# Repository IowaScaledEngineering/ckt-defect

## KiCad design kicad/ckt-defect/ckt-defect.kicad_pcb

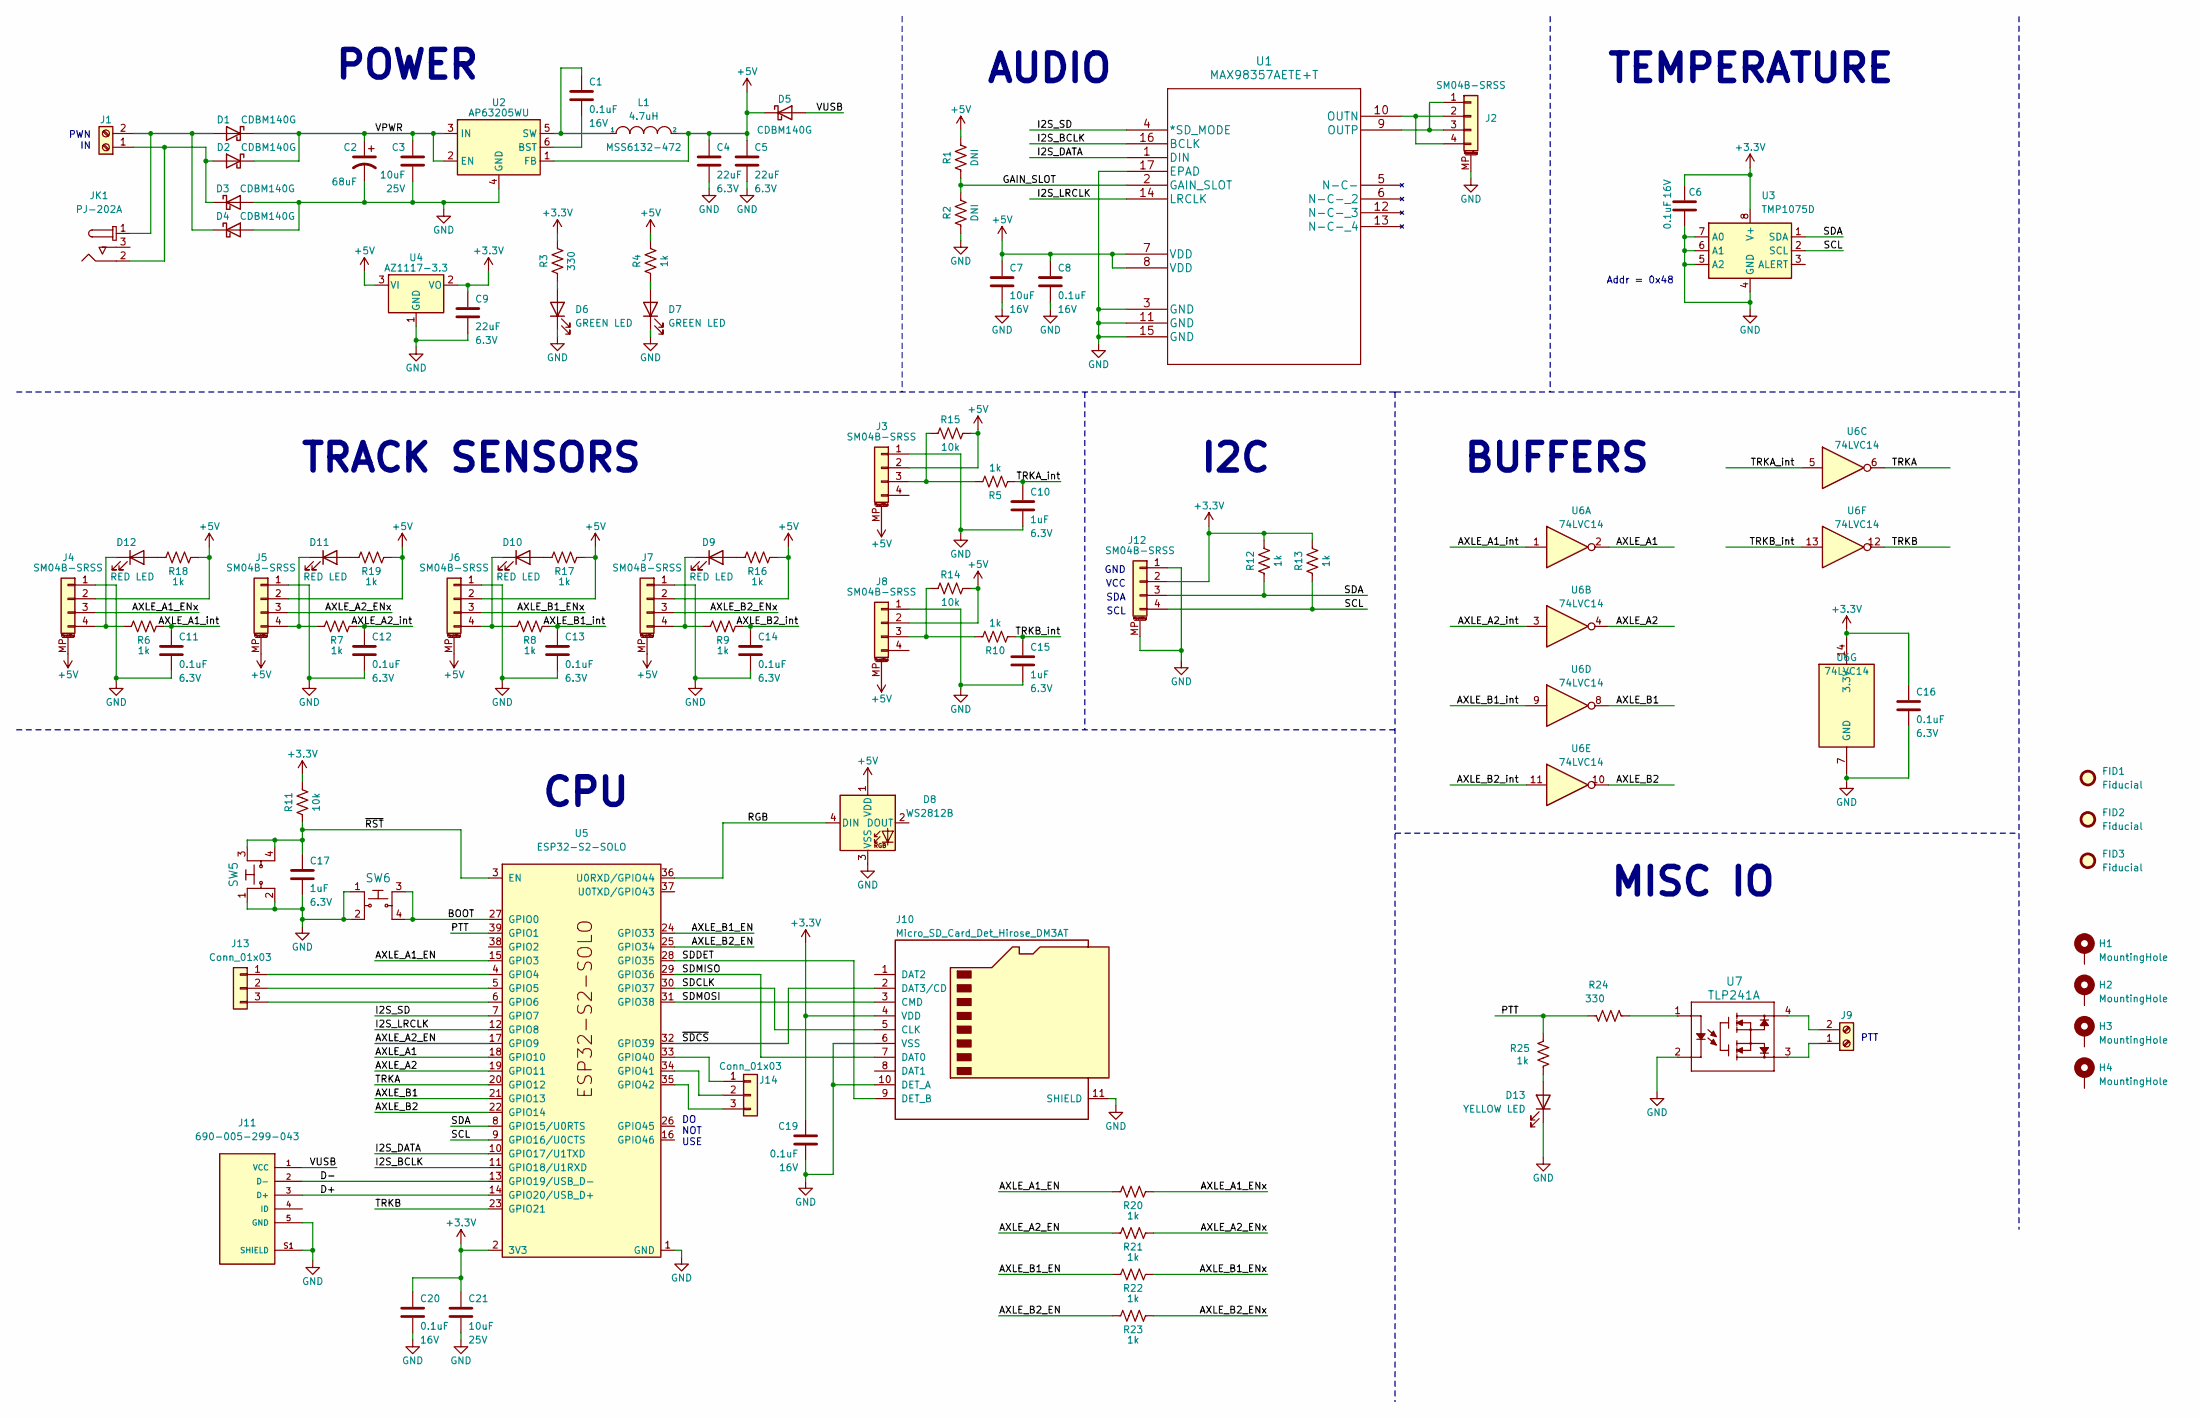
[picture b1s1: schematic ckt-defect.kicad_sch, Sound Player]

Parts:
C1, C6, C8, C19, C20: 0.1uF; C_0805_2012Metric; Voltage 16V
C2: 68uF; CP_Elec_6.3x5.8
C3, C21: 10uF; C_0805_2012Metric; Voltage 25V
C4, C5, C9: 22uF; C_0805_2012Metric; Voltage 6.3V
C7: 10uF; C_0805_2012Metric; Voltage 16V
C10, C15, C17: 1uF; C_0805_2012Metric; Voltage 6.3V
C11, C12, C13, C14, C16: 0.1uF; C_0805_2012Metric; Voltage 6.3V
D1, D2, D3, D4, D5: CDBM140G; SOD-123T
D6, D7: GREEN LED; LED_0805_2012Metric
D8: WS2812B; LED_WS2812B_PLCC4_5.0x5.0mm_P3.2mm
D9, D10, D11, D12: RED LED; LED_0805_2012Metric
D13: YELLOW LED; LED_0805_2012Metric
FID1, FID2, FID3: Fiducial; Fiducial_1mm_Mask2mm
H1, H2, H3, H4: MountingHole; MountingHole_3.2mm_M3_Pad
J1, J9: Screw_Terminal_01x02; TerminalBlock_RND_205-00012_1x02_P5.00mm_Horizontal
J2, J3, J4, J5, J6, J7, J8, J12: SM04B-SRSS; JST_SH_SM04B-SRSS-TB_1x04-1MP_P1.00mm_Horizontal
J10: Micro_SD_Card_Det_Hirose_DM3AT; microSD_HC_Hirose_DM3AT-SF-PEJM5
J11: 690-005-299-043; EDAC_690-005-299-043; PARTREV 11
J13, J14: Conn_01x03; PinHeader_1x03_P1.27mm_Vertical
JK1: PJ-202A; CUI_PJ-202A; MPN PJ-202A; Digi-Key_PN CP-202A-ND
L1: 4.7uH; MSS6132-xxxMLC
R1, R2: DNI; R_0805_2012Metric
R3, R24: 330; R_0805_2012Metric
R4, R5, R6, R7, R8, R9, R10, R12, R13, R16, R17, R18, R19, R20, R21, R22, R23, R25: 1k; R_0805_2012Metric
R11, R14, R15: 10k; R_0805_2012Metric
SW5, SW6: FSM4JSMA; TE_FSM4JSMA; MPN FSM4JSMATR; Digi-Key_PN 450-1759-1-ND
U1: MAX98357AETE+T; TQFN-16-1EP_3x3mm_P0.5mm_EP1.23x1.23mm
U2: AP63205WU; TSOT-23-6
U3: TMP1075D; SO-8_3.9x4.9mm_P1.27mm
U4: AZ1117-3.3; SOT-223-3_TabPin2
U5: ESP32-S2-SOLO
U6: 74LVC14; SOIC-14_3.9x8.7mm_P1.27mm
U7: TLP241A; 11-5B201S_TOS

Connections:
+3.3V: C6.1, C9.1, C16.1, C19.1, C20.1, C21.1, J10.4 (VDD), J12.2, R3.2, R11.2, R12.2, R13.2, U3.8 (V+), U4.2 (VO), U5.2 (3V3), U6.14 (3.3V)
+5V: C4.1, C5.1, C7.1, C8.1, D5.1 (K), D8.1 (VDD), J3.2, J3.MP (MountPin), J4.2, J4.MP (MountPin), J5.2, J5.MP (MountPin), J6.2, J6.MP (MountPin), J7.2, J7.MP (MountPin), J8.2, J8.MP (MountPin), L1.2, R1.2, R4.2, R14.2, R15.2, R16.1, R17.1, R18.1, R19.1, U1.7 (VDD), U1.8 (VDD), U2.1 (FB), U4.3 (VI)
/AXLE_A1: U5.18 (GPIO10), U6.2
/AXLE_A1_EN: R20.2, U5.15 (GPIO3)
/AXLE_A1_ENx: J4.3, R20.1
/AXLE_A1_int: C11.1, R6.1, U6.1
/AXLE_A2: U5.19 (GPIO11), U6.4
/AXLE_A2_EN: R21.2, U5.17 (GPIO9)
/AXLE_A2_ENx: J5.3, R21.1
/AXLE_A2_int: C12.1, R7.1, U6.3
/AXLE_B1: U5.21 (GPIO13), U6.8
/AXLE_B1_EN: R22.2, U5.24 (GPIO33)
/AXLE_B1_ENx: J6.3, R22.1
/AXLE_B1_int: C13.1, R8.1, U6.9
/AXLE_B2: U5.22 (GPIO14), U6.10
/AXLE_B2_EN: R23.2, U5.25 (GPIO34)
/AXLE_B2_ENx: J7.3, R23.1
/AXLE_B2_int: C14.1, R9.1, U6.11
/BOOT: SW6.3, SW6.4, U5.27 (GPIO0)
/D+: J11.3 (D+), U5.14 (GPIO20/USB_D+)
/D-: J11.2 (D-), U5.13 (GPIO19/USB_D-)
/GAIN_SLOT: R1.1, R2.2, U1.2 (GAIN_SLOT)
/I2S_BCLK: U1.16 (BCLK), U5.11 (GPIO18/U1RXD)
/I2S_DATA: U1.1 (DIN), U5.10 (GPIO17/U1TXD)
/I2S_LRCLK: U1.14 (LRCLK), U5.12 (GPIO8)
/I2S_SD: U1.4 (*SD_MODE), U5.7 (GPIO7)
/PTT: R24.2, R25.1, U5.39 (GPIO1)
/RGB: D8.4 (DIN), U5.36 (U0RXD/GPIO44)
/SCL: J12.4, R13.1, U3.2 (SCL), U5.9 (GPIO16/U0CTS)
/SDA: J12.3, R12.1, U3.1 (SDA), U5.8 (GPIO15/U0RTS)
/SDCLK: J10.5 (CLK), U5.30 (GPIO37)
/SDDET: J10.9 (DET_B), U5.28 (GPIO35)
/SDMISO: J10.7 (DAT0), U5.29 (GPIO36)
/SDMOSI: J10.3 (CMD), U5.31 (GPIO38)
/TRKA: U5.20 (GPIO12), U6.6
/TRKA_int: C10.1, R5.1, U6.5
/TRKB: U5.23 (GPIO21), U6.12
/TRKB_int: C15.1, R10.1, U6.13
/VPWR: C2.1, C3.1, D1.1 (K), D2.1 (K), U2.2 (EN), U2.3 (IN)
/VUSB: D5.2 (A), J11.1 (VCC)
/~RST: C17.1, R11.1, SW5.3, SW5.4, U5.3 (EN)
/~SDCS: J10.2 (DAT3/CD), U5.32 (GPIO39)
GND: C2.2, C3.2, C4.2, C5.2, C6.2, C7.2, C8.2, C9.2, C10.2, C11.2, C12.2, C13.2, C14.2, C15.2, C16.2, C17.2, C19.2, C20.2, C21.2, D3.2 (A), D4.2 (A), D6.1 (K), D7.1 (K), D8.3 (VSS), D13.1 (K), J2.MP (MountPin), J3.1, J4.1, J5.1, J6.1, J7.1, J8.1, J10.6 (VSS), J10.10 (DET_A), J10.11 (SHIELD), J11.5 (GND), J11.S1 (SHIELD), J12.1, J12.MP (MountPin), R2.1, SW5.1, SW5.2, SW6.1, SW6.2, U1.3 (GND), U1.11 (GND), U1.15 (GND), U1.17 (EPAD), U2.4 (GND), U3.4 (GND), U3.5 (A2), U3.6 (A1), U3.7 (A0), U4.1 (GND), U5.1 (GND), U5.40 (GND), U5.41 (GND), U6.7 (GND), U7.2
unnamed: D1.2 (A), D4.1 (K), J1.2, JK1.1
unnamed: D2.2 (A), D3.1 (K), J1.1, JK1.2
unnamed: D6.2 (A), R3.1
unnamed: D7.2 (A), R4.1
unnamed: D9.2 (A), R16.2
unnamed: D9.1 (K), J7.4, R9.2
unnamed: D10.2 (A), R17.2
unnamed: D10.1 (K), J6.4, R8.2
unnamed: D11.2 (A), R19.2
unnamed: D11.1 (K), J5.4, R7.2
unnamed: D12.2 (A), R18.2
unnamed: D12.1 (K), J4.4, R6.2
unnamed: D13.2 (A), R25.2
unnamed: J2.1, J2.3, U1.9 (OUTP)
unnamed: J2.2, J2.4, U1.10 (OUTN)
unnamed: J3.3, R5.2, R15.1
unnamed: J8.3, R10.2, R14.1
unnamed: J9.1, U7.3
unnamed: J9.2, U7.4
unnamed: J13.1, U5.4 (GPIO4)
unnamed: J13.2, U5.5 (GPIO5)
unnamed: J13.3, U5.6 (GPIO6)
unnamed: J14.1, U5.33 (GPIO40)
unnamed: J14.2, U5.34 (GPIO41)
unnamed: J14.3, U5.35 (GPIO42)
unnamed: R24.1, U7.1
unnamed: C1.2, U2.6 (BST)
unnamed: C1.1, L1.1, U2.5 (SW)

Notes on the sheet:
BUFFERS
DO NOT USE
GND
PTT
I2C
TEMPERATURE
PWN IN
POWER
TRACK SENSORS
Addr = 0x48
CPU
SDA
MISC IO
AUDIO
VCC
SCL

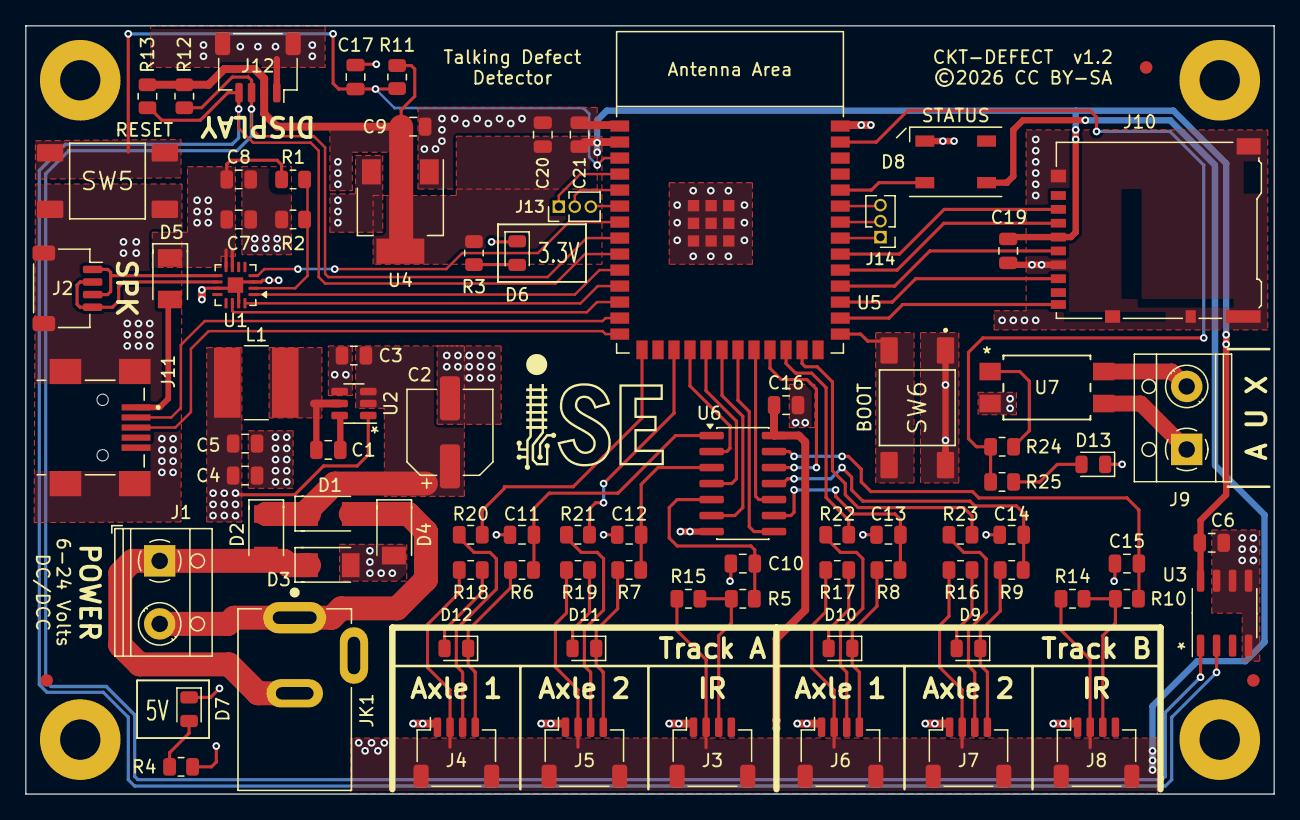
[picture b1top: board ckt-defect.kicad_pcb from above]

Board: 2 copper layers, 99.1 x 61.0 mm, 90 parts (0 on the bottom side), 71 nets.

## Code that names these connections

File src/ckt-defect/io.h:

/*************************************************************************
Title:    Input/Output Functions
Authors:  Michael Petersen <railfan@drgw.net>
File:     io.h
License:  GNU General Public License v3

LICENSE:
    Copyright (C) 2026 Michael Petersen & Nathan Holmes

    This program is free software; you can redistribute it and/or modify
    it under the terms of the GNU General Public License as published by
    the Free Software Foundation; either version 2 of the License, or
    any later version.

    This program is distributed in the hope that it will be useful,
    but WITHOUT ANY WARRANTY; without even the implied warranty of
    MERCHANTABILITY or FITNESS FOR A PARTICULAR PURPOSE.  See the
    GNU General Public License for more details.

*************************************************************************/

#pragma once

// Pins
#define SDA          GPIO_NUM_15
#define SCL          GPIO_NUM_16
#define I2S_SD       GPIO_NUM_7
#define I2S_DOUT     GPIO_NUM_17
#define I2S_BCLK     GPIO_NUM_18
#define I2S_LRCLK    GPIO_NUM_8
#define SDCLK        37
#define SDMOSI       38
#define SDMISO       36
#define SDCS         39
#define SDDET        GPIO_NUM_35

#define AXLE_A1      GPIO_NUM_10
#define AXLE_A1_EN   GPIO_NUM_3
#define AXLE_A2      GPIO_NUM_11
#define AXLE_A2_EN   GPIO_NUM_9
#define AXLE_B1      GPIO_NUM_13
#define AXLE_B1_EN   GPIO_NUM_33
#define AXLE_B2      GPIO_NUM_14
#define AXLE_B2_EN   GPIO_NUM_34
#define TRKA         GPIO_NUM_12
#define TRKB         GPIO_NUM_21

#define AUX          GPIO_NUM_1

#define TP0          GPIO_NUM_4
#define TP1          GPIO_NUM_5
#define TP2          GPIO_NUM_6
#define TP3          GPIO_NUM_40
#define TP4          GPIO_NUM_41
#define TP5          GPIO_NUM_42

void ioInit(void);

void enableAuxRelay(void);
void disableAuxRelay(void);

void ioProcessInputs(void);
bool getIrA(void);
bool getAxleA1(void);
bool getAxleA2(void);
bool getIrB(void);
bool getAxleB1(void);
bool getAxleB2(void);

void setTestPoint(gpio_num_t tp);
void clrTestPoint(gpio_num_t tp);

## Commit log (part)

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2025-06-30 Sent to fab
2025-12-28 Renamed to ckt-defect
2025-12-28 Copied latest code from snd-player
2025-12-28 Updated makefile
2025-12-29 Task based audio feeder
2025-12-29 Removed PLAYER_RETRY state and used blocking feature of i2s_channel_write
2025-12-29 Cleaned up task delay when in idle state
2025-12-29 Split out I2S code into its own file
2025-12-29 Moved volume handling to audio files. Cleaned up restart code.
2025-12-29 Cleanup
2025-12-30 Some cleanup in the silence generation
2026-02-12 Copy from snd-player and modified
2026-02-12 Kicad 9 conversion; added test points
2026-03-07 Some rip-up and refactoring, with a dash of architecture
2026-03-08 More progress
2026-03-08 Minor updates
2026-03-08 vocab support files
2026-03-08 Refactored audio code to wrap queue handling in functions
2026-03-08 Some changes
2026-03-08 Moved sound functions into cpp
2026-03-08 More improvements
2026-03-08 sound function refactoring to use std::string
2026-03-08 First cut at internal vocab
2026-03-08 vocab cleanup
2026-03-09 Initial parser code
2026-03-09 Some updates
2026-03-09 Searchable vocab
2026-03-09 Parsing and reading messages
2026-03-12 Updated parser to accept a ParserObject and optionally delete the message when done.
2026-03-13 Some documents
2026-03-14 Added message transformation
2026-03-14 More parsing and a better test state machine
2026-03-14 Removed debug message
2026-03-14 Added tone support
2026-03-14 Added "detector out" to exit message
2026-03-15 Initial axle simulator
2026-03-15 Working axle simulator
2026-03-15 Axle calculator
2026-03-15 Changed axle counters to use 3.3V supply
2026-03-15 Updated date
2026-03-15 Moved axles simulator over to ckt-axle project
2026-03-15 IO functions and LCD test code
2026-03-15 Aux relay support
2026-03-16 Added test points for profiling
2026-03-16 Changed edge cleanance
2026-03-16 Adjusted the 5V bus at the bottom
2026-03-16 Initial axle counter interrupts
2026-03-18 Added input schmitt inverters
2026-03-18 Moved logo
2026-03-18 Changed to micros()
2026-03-19 Improved buffering
2026-03-19 PG 1.1
2026-03-21 Added PTT support to the audio driver
2026-03-21 Refactored axle counter code
2026-03-22 Changed to Kicad footprint for QFN
2026-04-05 Added sound effects
2026-04-06 Added programmability to tone generation
2026-04-06 Added programmable silence
2026-04-14 Refactoring for SD card
2026-04-14 Axle counter code fixed
2026-05-17 Added menu code - untested
2026-05-18 Updated menu code
2026-05-18 Remove executable
2026-05-18 Initial cache LCD implementation
2026-05-18 gotoxy fixes
2026-05-18 Improved string writes
2026-05-18 Fixed excess overwrites
2026-05-23 Removed brackets from MenuNumberDial
2026-05-23 Added leading zero suppression option in MenuDigitThumbwheel
2026-05-23 Added backlight code
2026-05-23 Fixed brightness value when writing I2C
2026-05-23 Added NACK detection and refreshing
2026-05-23 Added custom character support
2026-05-23 Fixed hardware vs software brightness levels
2026-05-23 Initial brightness menu
2026-05-23 Updated brightness menu with 16 levels
2026-05-23 Swapped +/- button on NumberDial
2026-05-23 Removed debug code
2026-05-23 Default backlight off
2026-05-23 Added MenuPercentageBar
2026-05-23 Removed MenuBacklight and updated MenuPercentageBar to accept getter/setter functions
2026-05-24 Added getter/setter support to all menus
2026-05-24 Moved realTime argument
2026-05-24 Formatting cleanup
2026-05-24 Changed display connect wait to 100ms
2026-05-24 Added realTimeUpdate to all versions of constructors
2026-05-24 Added save callback
2026-05-24 Added LCD brightness handling
2026-05-24 Added continuous increment/decrement
2026-05-24 Added auto-increment
2026-05-24 Removed timing logic from MenuBoolSelector
2026-05-24 Refactoring and cleanup
2026-05-24 Refactored out common code
2026-05-24 Added volume menu
2026-05-25 New menu-custom.cpp file
2026-05-25 Added onEnter function
2026-05-25 Rearranged and condensed menus
2026-05-25 Added long press support
2026-05-25 Changed UP/DOWN to PRESS/RELEASE
2026-05-25 Fixed typo
2026-05-25 Added longHoldDelay
2026-05-25 Updated long press support
2026-05-25 Implement long press
2026-05-27 Added speed and axle variables
2026-05-30 Added splash screen
2026-05-30 Fixed tag logic
2026-06-02 Changed function name
2026-06-12 Menu cleanup
2026-06-12 Reduced to one set of track messages
2026-06-12 Added track name string
2026-06-12 Added track name selection
2026-06-12 Added words
2026-06-12 Fixed vocab files
2026-06-12 Voice files
2026-06-12 Refactored track name visibility code
2026-06-12 Added milepost menu and supporting code
2026-06-13 Delay backlight off
2026-06-14 Refactoring
2026-06-14 Better milepost handling
2026-06-14 Updated backlight control
2026-06-14 Moved trackName setting to main loop
2026-06-18 Some refactoring
2026-06-18 Refactored menu code into separate file
2026-06-18 Removed extra display parameter
2026-06-18 Changed backlight button text
2026-06-18 Added axle menu and basic speed menu
2026-06-21 Added fixme reminders
2026-06-21 Added speed menus
2026-06-21 Refactored to improve menu hiding/unhiding
2026-06-21 Fixed padding in Bool menu
2026-06-21 Updated speed menus
2026-06-21 Added detector timeout and cleaned up speed units
2026-06-21 Better track name handling
2026-06-21 Added temperature menus
2026-06-21 Added support for negative numbers in NumberDial
2026-06-21 Menu name cleanup
2026-06-21 Added load/save/print for tempreature configs
2026-06-27 Updated kicad data
2026-06-27 Added IR state machine
2026-06-28 Added axle state machine
2026-06-28 Added main state machine, refactored some IR/axle state machine code.
2026-06-28 Refactored state machine code
2026-06-28 Added state transition code
2026-06-28 Added comment
2026-06-28 Added nvm usage report
2026-06-28 Refactored axle state enum
2026-06-28 Variables for direction
2026-06-28 Added direction configuration
2026-06-28 Added infrastructure mode configuration
2026-06-28 Starting main state machine implementation
2026-06-28 Added random generator
2026-06-28 Create trigger menu and moved direction triggers there
2026-06-28 Added message bundle to state machines

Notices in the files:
kicad/ckt-defect/ckt-defect.kicad_pcb:
©2026 CC BY-SA
